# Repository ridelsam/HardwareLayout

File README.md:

# HardwareLayout
repo for hardware layout projects (altium, kicad)

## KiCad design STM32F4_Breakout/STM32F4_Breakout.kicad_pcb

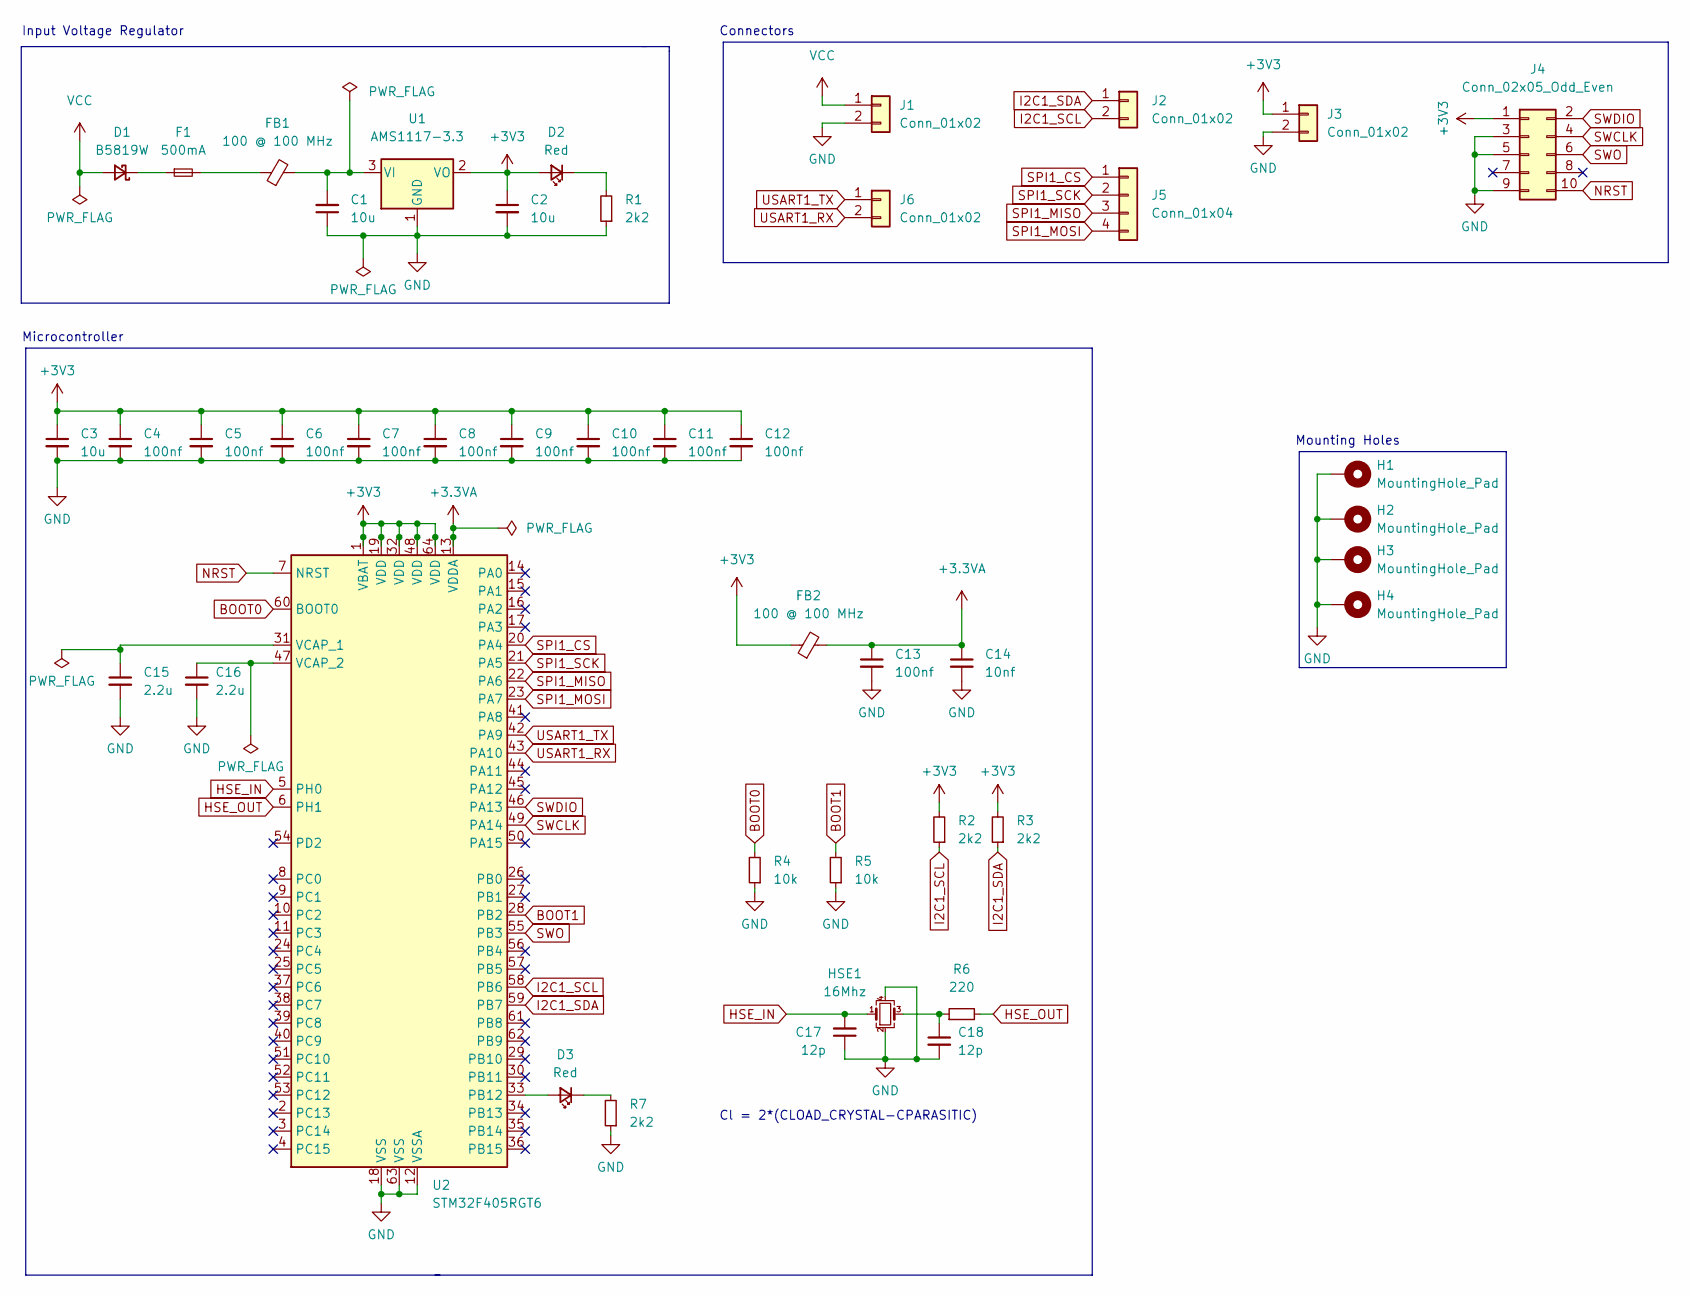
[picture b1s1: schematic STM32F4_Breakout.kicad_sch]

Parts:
C1, C2: 10u; C_0805_2012Metric
C3: 10u; C_0603_1608Metric
C4, C5, C6, C7, C8, C9, C10, C11, C12, C13: 100nf; C_0402_1005Metric
C14: 10nf; C_0402_1005Metric
C15, C16: 2.2u; C_0603_1608Metric
C17, C18: 12p; C_0402_1005Metric
D1: B5819W; D_SOD-123
D2, D3: Red; LED_0603_1608Metric
F1: 500mA; Fuse_0603_1608Metric
FB1, FB2: 100 @ 100 MHz; L_0805_2012Metric
H1, H2, H3, H4: MountingHole_Pad; MountingHole_4.3mm_M4_Pad_Via
HSE1: 16Mhz; Crystal_SMD_3225-4Pin_3.2x2.5mm
J1, J2, J3, J6: Conn_01x02; PinHeader_1x02_P2.54mm_Vertical
J4: Conn_02x05_Odd_Even; PinHeader_2x05_P1.27mm_Vertical_SMD
J5: Conn_01x04; PinHeader_1x04_P2.54mm_Vertical
R1, R7: 2k2; R_0603_1608Metric
R2, R3: 2k2; R_0402_1005Metric
R4, R5: 10k; R_0402_1005Metric
R6: 220; R_0402_1005Metric
U1: AMS1117-3.3; SOT-223-3_TabPin2
U2: STM32F405RGT6; LQFP-64_10x10mm_P0.5mm

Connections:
+3.3VA: C13.1, C14.1, FB2.2, U2.13 (VDDA)
+3V3: C2.1, C3.1, C4.1, C5.1, C6.1, C7.1, C8.1, C9.1, C10.1, C11.1, C12.1, D2.2 (A), FB2.1, J3.1, J4.1, R2.2, R3.2, U1.2 (VO), U2.1 (VBAT), U2.19 (VDD), U2.32 (VDD), U2.48 (VDD), U2.64 (VDD)
BOOT0: R4.2, U2.60 (BOOT0)
BOOT1: R5.2, U2.28 (PB2)
GND: C1.1, C2.2, C3.2, C4.2, C5.2, C6.2, C7.2, C8.2, C9.2, C10.2, C11.2, C12.2, C13.2, C14.2, C15.2, C16.2, C17.1, C18.2, H1.1, H2.1, H3.1, H4.1, HSE1.2, HSE1.4, J1.2, J3.2, J4.3, J4.5, J4.9, R1.1, R4.1, R5.1, R7.1, U1.1 (GND), U2.12 (VSSA), U2.18 (VSS), U2.63 (VSS)
HSE_IN: C17.2, HSE1.1, U2.5 (PH0)
HSE_OUT: R6.2, U2.6 (PH1)
I2C1_SCL: J2.2, R2.1, U2.58 (PB6)
I2C1_SDA: J2.1, R3.1, U2.59 (PB7)
NRST: J4.10, U2.7 (NRST)
unnamed: C1.2, FB1.2, U1.3 (VI)
unnamed: C15.1, U2.31 (VCAP_1)
unnamed: C16.1, U2.47 (VCAP_2)
unnamed: C18.1, HSE1.3, R6.1
unnamed: D1.1 (K), F1.1
unnamed: D2.1 (K), R1.2
unnamed: D3.1 (K), R7.2
unnamed: D3.2 (A), U2.33 (PB12)
unnamed: F1.2, FB1.1
SPI1_CS: J5.1, U2.20 (PA4)
SPI1_MISO: J5.3, U2.22 (PA6)
SPI1_MOSI: J5.4, U2.23 (PA7)
SPI1_SCK: J5.2, U2.21 (PA5)
SWCLK: J4.4, U2.49 (PA14)
SWDIO: J4.2, U2.46 (PA13)
SWO: J4.6, U2.55 (PB3)
USART1_RX: J6.2, U2.43 (PA10)
USART1_TX: J6.1, U2.42 (PA9)
VCC: D1.2 (A), J1.1

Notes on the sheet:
Input Voltage Regulator
Microcontroller
Connectors
Cl = 2*(CLOAD_CRYSTAL-CPARASITIC)
Mounting Holes

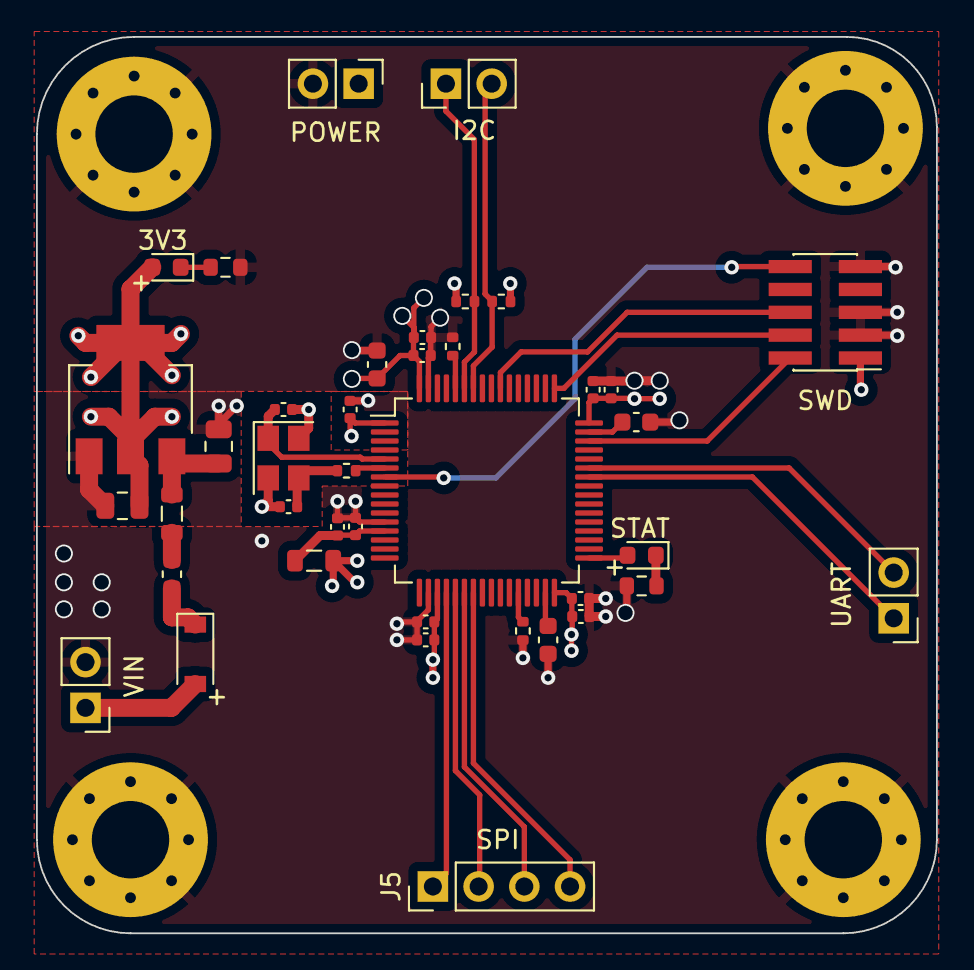
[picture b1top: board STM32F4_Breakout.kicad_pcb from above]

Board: 4 copper layers, 50.0 x 49.8 mm, 44 parts (0 on the bottom side), 29 nets.

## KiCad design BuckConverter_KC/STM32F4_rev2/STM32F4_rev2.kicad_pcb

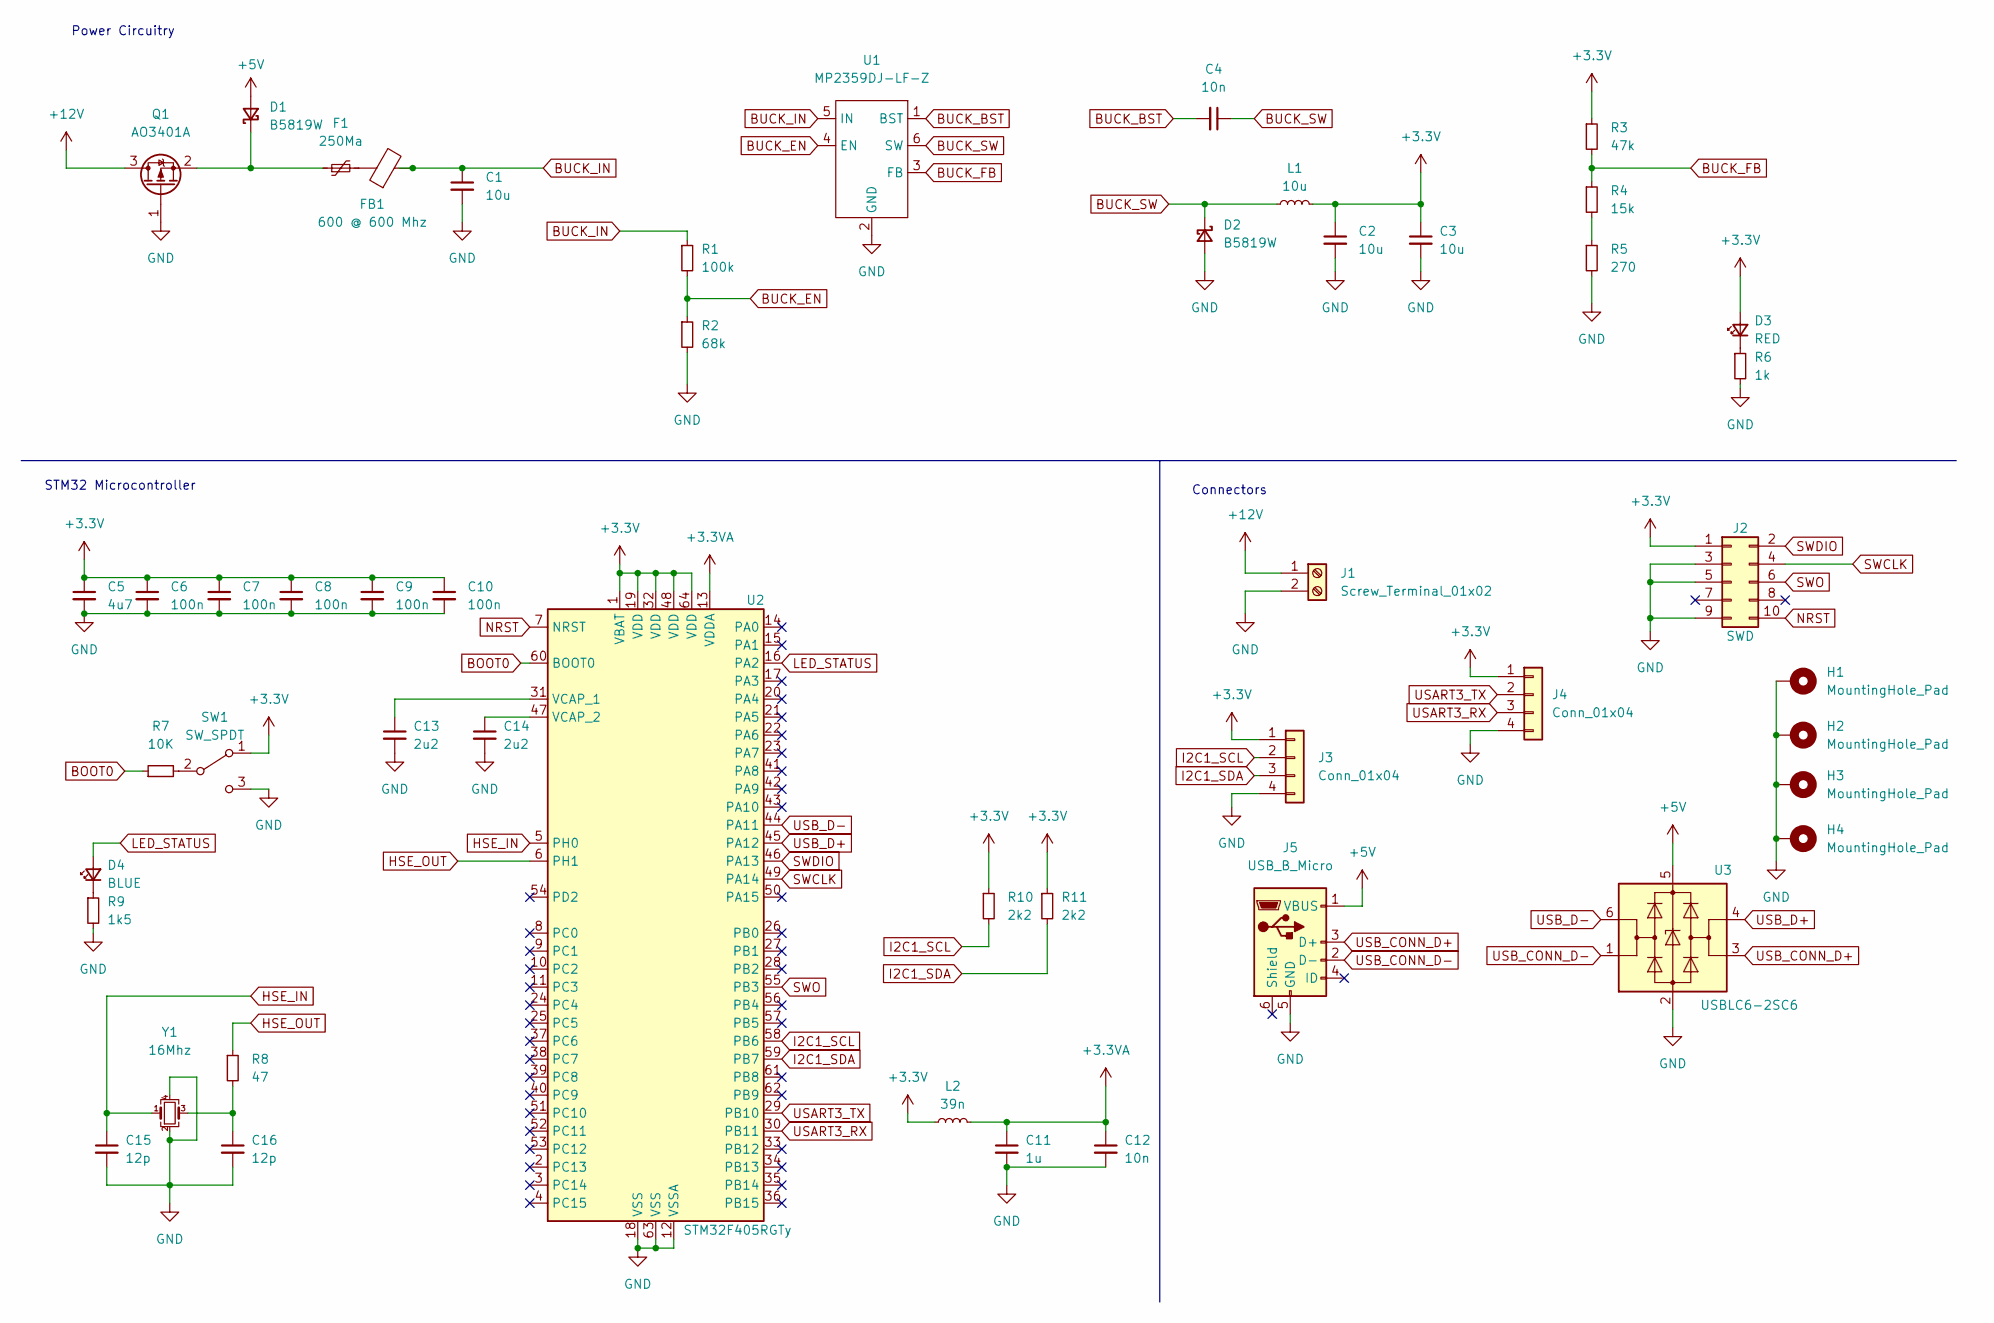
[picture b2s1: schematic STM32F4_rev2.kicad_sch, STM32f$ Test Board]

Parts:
C1, C2, C3: 10u; C_1206_3216Metric
C4: 10n; C_0603_1608Metric
C5: 4u7; C_0603_1608Metric
C6, C7, C8, C9, C10: 100n; C_0402_1005Metric
C11: 1u; C_0402_1005Metric
C12: 10n; C_0402_1005Metric
C13, C14: 2u2; C_0603_1608Metric
C15, C16: 12p; C_0402_1005Metric
D1, D2: B5819W; D_SOD-123
D3: RED; D_0603_1608Metric
D4: BLUE; D_0603_1608Metric
F1: 250Ma; Fuse_1206_3216Metric
FB1: 600 @ 600 Mhz; L_0805_2012Metric
H1, H2, H3, H4: MountingHole_Pad; MountingHole_4.3mm_M4_Pad_Via
J1: Screw_Terminal_01x02; TerminalBlock_Phoenix_PT-1,5-2-3.5-H_1x02_P3.50mm_Horizontal
J2: SWD; PinHeader_2x05_P1.27mm_Vertical_SMD
J3, J4: Conn_01x04; Molex_PicoBlade_53048-0410_1x04_P1.25mm_Horizontal
J5: USB_B_Micro; USB_Micro-B_Amphenol_10103594-0001LF_Horizontal
L1: 10u; L_Sunlord_MWSA0518_5.4x5.2mm
L2: 39n; L_0402_1005Metric
Q1: AO3401A; SOT-23
R1: 100k; R_0603_1608Metric
R2: 68k; R_0603_1608Metric
R3: 47k; R_0603_1608Metric
R4: 15k; R_0603_1608Metric
R5: 270; R_0603_1608Metric
R6: 1k; R_0603_1608Metric
R7: 10K; R_0402_1005Metric
R8: 47; R_0402_1005Metric
R9: 1k5; R_0603_1608Metric
R10, R11: 2k2; R_0402_1005Metric
SW1: SW_SPDT; SW_SPDT_PCM12
U1: MP2359DJ-LF-Z; SOT-23-6
U2: STM32F405RGTy; LQFP-64_10x10mm_P0.5mm
U3: USBLC6-2SC6; SOT-23-6
Y1: 16Mhz; Crystal_SMD_3225-4Pin_3.2x2.5mm

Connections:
+3.3V: C2.1, C3.1, C5.1, C6.1, C7.1, C8.1, C9.1, C10.1, D3.2 (A), J2.1, J3.1, J4.1, L1.2, L2.1, R3.1, R10.1, R11.1, SW1.1 (A), U2.1 (VBAT), U2.19 (VDD), U2.32 (VDD), U2.48 (VDD), U2.64 (VDD)
+3.3VA: C11.1, C12.1, L2.2, U2.13 (VDDA)
+5V: D1.2 (A), J5.1 (VBUS), U3.5 (VBUS)
+12V: J1.1, Q1.3 (D)
BOOT0: R7.1, U2.60 (BOOT0)
BUCK_BST: C4.2, U1.1 (BST)
BUCK_EN: R1.2, R2.1, U1.4 (EN)
BUCK_FB: R3.2, R4.1, U1.3 (FB)
BUCK_IN: C1.1, FB1.2, R1.1, U1.5 (IN)
BUCK_SW: C4.1, D2.1 (K), L1.1, U1.6 (SW)
GND: C1.2, C2.2, C3.2, C5.2, C6.2, C7.2, C8.2, C9.2, C10.2, C11.2, C12.2, C13.2, C14.2, C15.2, C16.2, D2.2 (A), H1.1, H2.1, H3.1, H4.1, J1.2, J2.3, J2.5, J2.9, J3.4, J4.4, J5.5 (GND), Q1.1 (G), R2.2, R5.2, R6.2, R9.2, SW1.3 (C), U1.2 (GND), U2.12 (VSSA), U2.18 (VSS), U2.63 (VSS), U3.2 (GND), Y1.2, Y1.4
HSE_IN: C15.1, U2.5 (PH0), Y1.1
HSE_OUT: R8.1, U2.6 (PH1)
I2C1_SCL: J3.2, R10.2, U2.58 (PB6)
I2C1_SDA: J3.3, R11.2, U2.59 (PB7)
LED_STATUS: D4.2 (A), U2.16 (PA2)
NRST: J2.10, U2.7 (NRST)
unnamed: C13.1, U2.31 (VCAP_1)
unnamed: C14.1, U2.47 (VCAP_2)
unnamed: C16.1, R8.2, Y1.3
unnamed: D1.1 (K), F1.1, Q1.2 (S)
unnamed: D3.1 (K), R6.1
unnamed: D4.1 (K), R9.1
unnamed: F1.2, FB1.1
unnamed: R4.2, R5.1
unnamed: R7.2, SW1.2 (B)
SWCLK: J2.4, U2.49 (PA14)
SWDIO: J2.2, U2.46 (PA13)
SWO: J2.6, U2.55 (PB3)
USART3_RX: J4.3, U2.30 (PB11)
USART3_TX: J4.2, U2.29 (PB10)
USB_CONN_D+: J5.3 (D+), U3.3 (I/O2)
USB_CONN_D-: J5.2 (D-), U3.1 (I/O1)
USB_D+: U2.45 (PA12), U3.4 (I/O2)
USB_D-: U2.44 (PA11), U3.6 (I/O1)

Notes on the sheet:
Connectors
Power Circuitry
STM32 Microcontroller

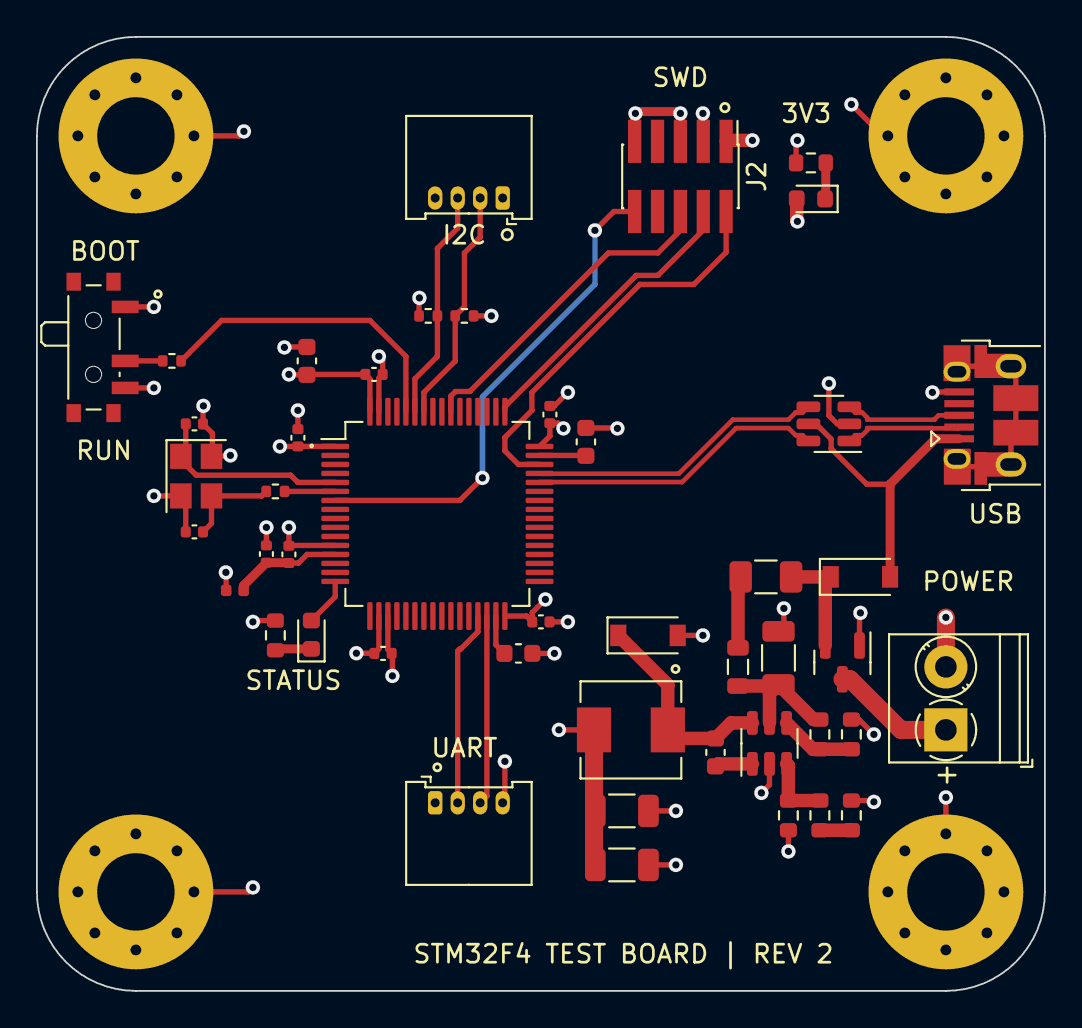
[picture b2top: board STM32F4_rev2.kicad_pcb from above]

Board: 4 copper layers, 56.0 x 53.0 mm, 50 parts (0 on the bottom side), 35 nets.

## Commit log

2022-09-17 buck converter initial commit
2022-09-20 finished stm32, power and basic connector schematic; added parts in library; deleted backup files
2022-09-21 finished schematic (added usb, mounting holes, add labels); started layout
2022-09-22 finished layout less the 3v3 and gnd
2022-09-23 finished layout; generated gerber, component footprints position files, BOM
2022-12-04 adding simple LED project to hardware layout folder
2022-12-04 updating BuckConverter project
2022-12-05 arduino clone project using Altium from Fedevel ucontroller course 12/2021
2022-12-05 updating git ignore file
2022-12-05 Power Supply project using ISL6236A chip; Fedevel Academy Course 1/2022
2022-12-05 misc file: notes, 3D models
2023-04-27 starting stm32f4 breakout layout project with kicad; updating git ignore file
2023-04-28 Setting up power supply (regulation, protection, filtering)
2023-04-29 adding decoupling caps, vdda filtering, bootmodes
2023-04-30 crystal oscillator (HSE, Load Capacitors, Feed resistor)
2023-04-30 serial wire debug; pin assignments and peripheral selection in CubeMX
2023-05-02 adding connectors, test points and mounting holes
2023-05-03 adding labels, annotation and running ERC
2023-05-04 Component/footprint sizing, selection and assignment
2023-05-05 board sizing and mounting hole placement
2023-05-09 resizing and shaping board
2023-05-10 rough placement of filtering caps, ucontroller and oscillator circuit
2023-05-11 finishing ucontroller layout
2023-05-12 laying out power supply and connectors
2023-05-14 setting up layers and design rules per jlcpcb
2023-05-15 fixing issue with the layer power plane assignment
2023-05-16 fixing copper ours and gnd polygon around crystal
2023-05-17 routing crystal oscillator per datasheet
2023-05-26 routed power lines and debug connector
2023-05-28 power and ground connections (vias)
2023-05-30 silkscreen labeling; gerber and drill file generation; BoM
